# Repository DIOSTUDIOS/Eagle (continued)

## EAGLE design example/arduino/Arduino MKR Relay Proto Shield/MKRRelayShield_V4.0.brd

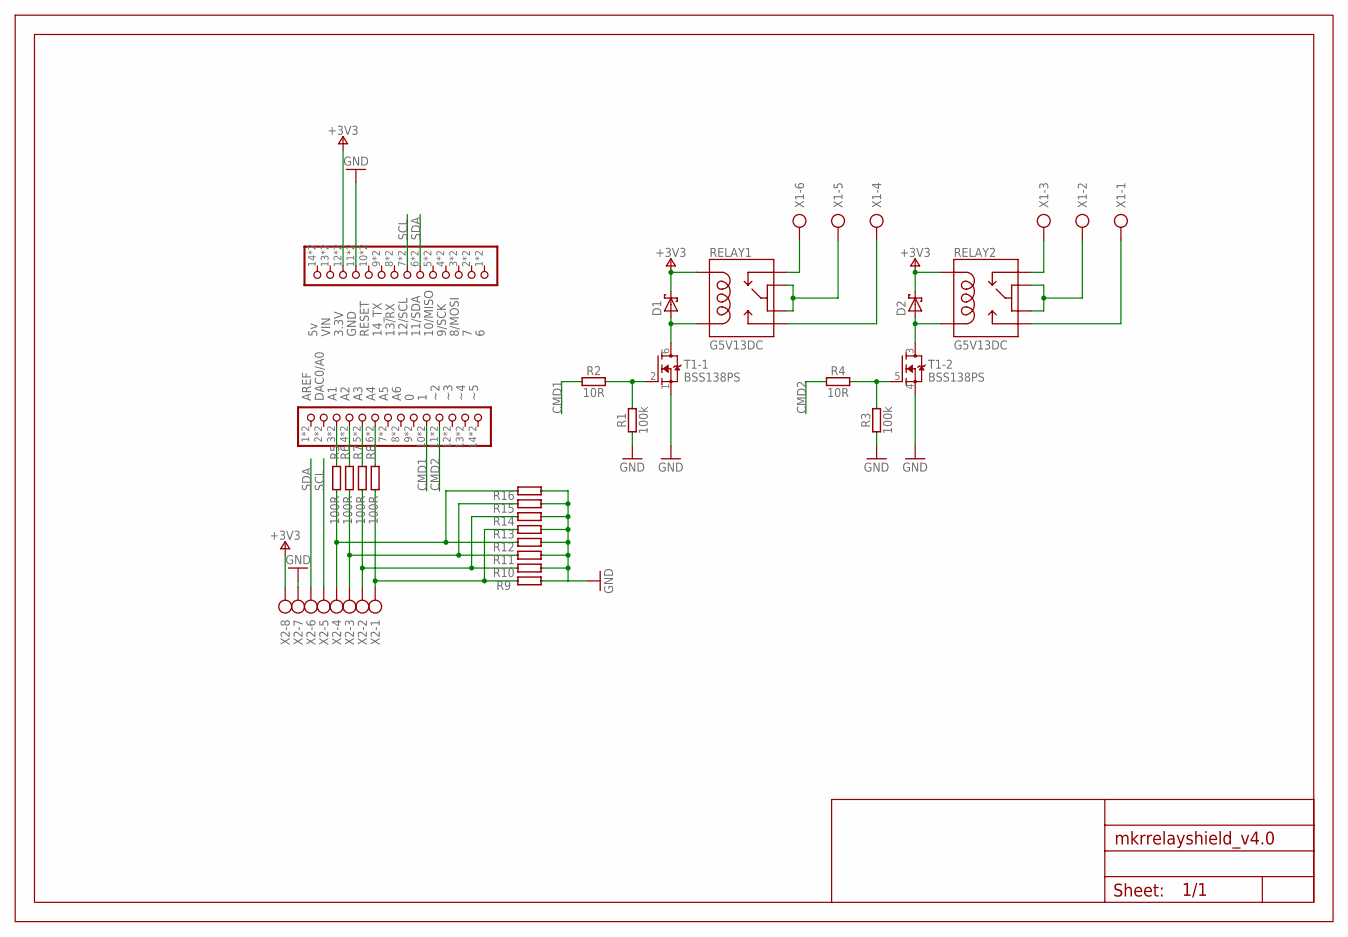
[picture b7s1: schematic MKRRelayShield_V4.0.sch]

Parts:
D1, D2: D_SCHOTTKYSO123; SMA_DO123
FRAME1: DNP; FRAME
JP3, JP4: PINHD-1X14DOUBLE; 1X14-DOUBLE
R1, R3: 100k; 0402-1005X55N
R2, R4: 10R; 0402-1005X55N
R5, R6, R7, R8, R13, R14, R15, R16: 100R; 0805-R2013X50N
R9, R10, R11, R12: 10k; 0204V
RELAY1, RELAY2: G5V13DC; RELAY-G5V
T1: BSS138PS; SOT363
X1: AK300/6
X2: AK300/8

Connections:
+3V3: D1.C, D2.C, JP4.12, JP4.26 (12), RELAY1.2, RELAY2.2, X2.8
CMD1: JP3.10, JP3.24 (10), R2.1
CMD2: JP3.11, JP3.25 (11), R4.1
GND: JP4.11, JP4.25 (11), R1.1, R3.1, R9.1, R10.1, R11.1, R12.1, R13.1, R14.1, R15.1, R16.1, T1.1 (S), T1.4 (S), X2.7
unnamed: JP3.6, JP3.20 (6), R8.2
unnamed: R5.1, R12.2, R16.2, X2.4
unnamed: JP3.5, JP3.19 (5), R7.2
unnamed: JP3.4, JP3.18 (4), R6.2
unnamed: JP3.3, JP3.17 (3), R5.2
unnamed: R6.1, R11.2, R15.2, X2.3
unnamed: R7.1, R10.2, R14.2, X2.2
unnamed: R8.1, R9.2, R13.2, X2.1
unnamed: RELAY1.5, RELAY1.6, X1.5
unnamed: D1.A, RELAY1.9, T1.6 (D)
unnamed: RELAY2.5, RELAY2.6, X1.2
unnamed: D2.A, RELAY2.9, T1.3 (D)
unnamed: RELAY1.1, X1.6
unnamed: RELAY1.10, X1.4
unnamed: RELAY2.1, X1.3
unnamed: RELAY2.10, X1.1
unnamed: R1.2, R2.2, T1.2 (G)
unnamed: R3.2, R4.2, T1.5 (G)
SCL: JP4.7, JP4.21 (7), X2.5
SDA: JP4.6, JP4.20 (6), X2.6

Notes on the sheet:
AREF
DAC0/A0
8/MOSI
9/SCK
10/MISO
11/SDA
12/SCL
13/RX
14_TX
RESET
GND
3.3V
VIN

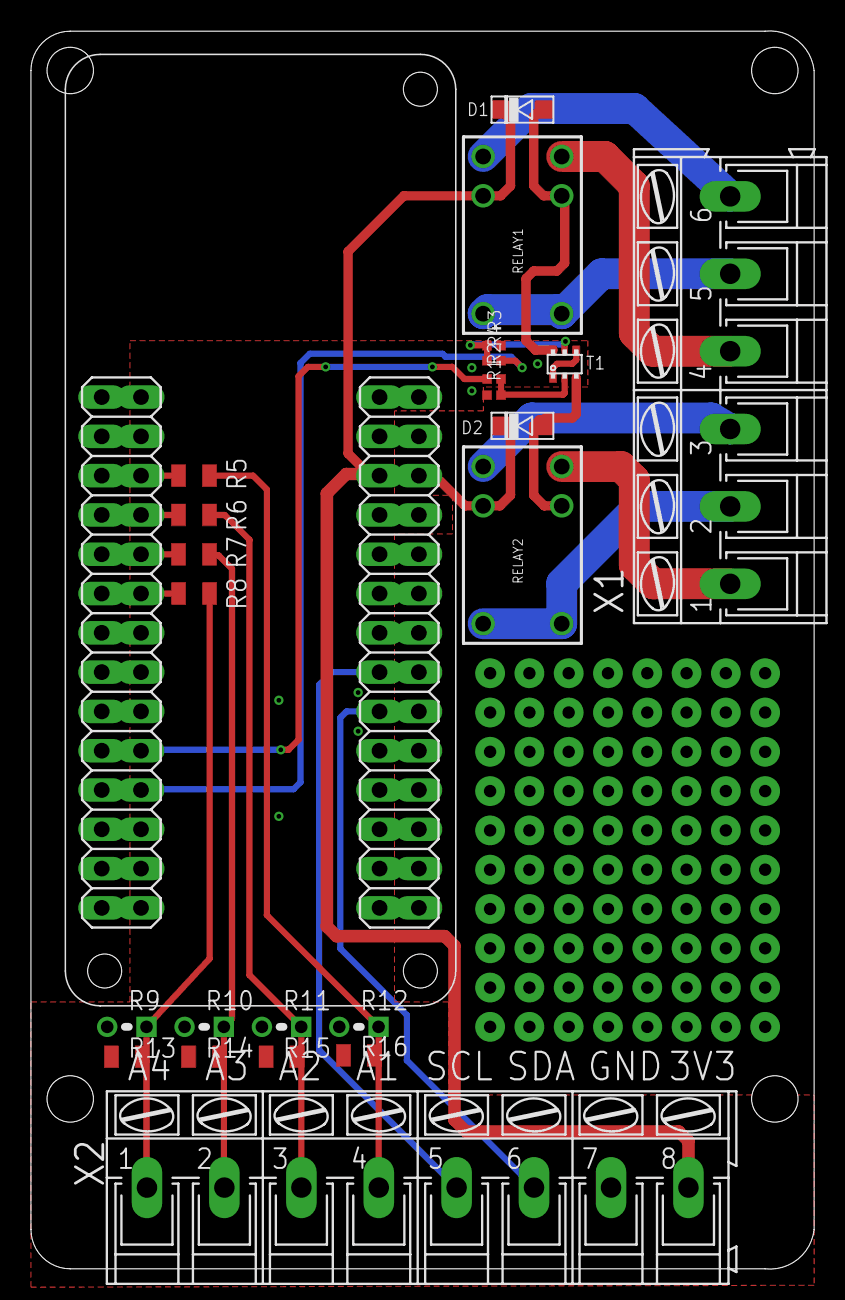
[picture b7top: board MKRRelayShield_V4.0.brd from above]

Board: 2 copper layers, 50.6 x 80.0 mm, 26 parts (0 on the bottom side), 24 nets.

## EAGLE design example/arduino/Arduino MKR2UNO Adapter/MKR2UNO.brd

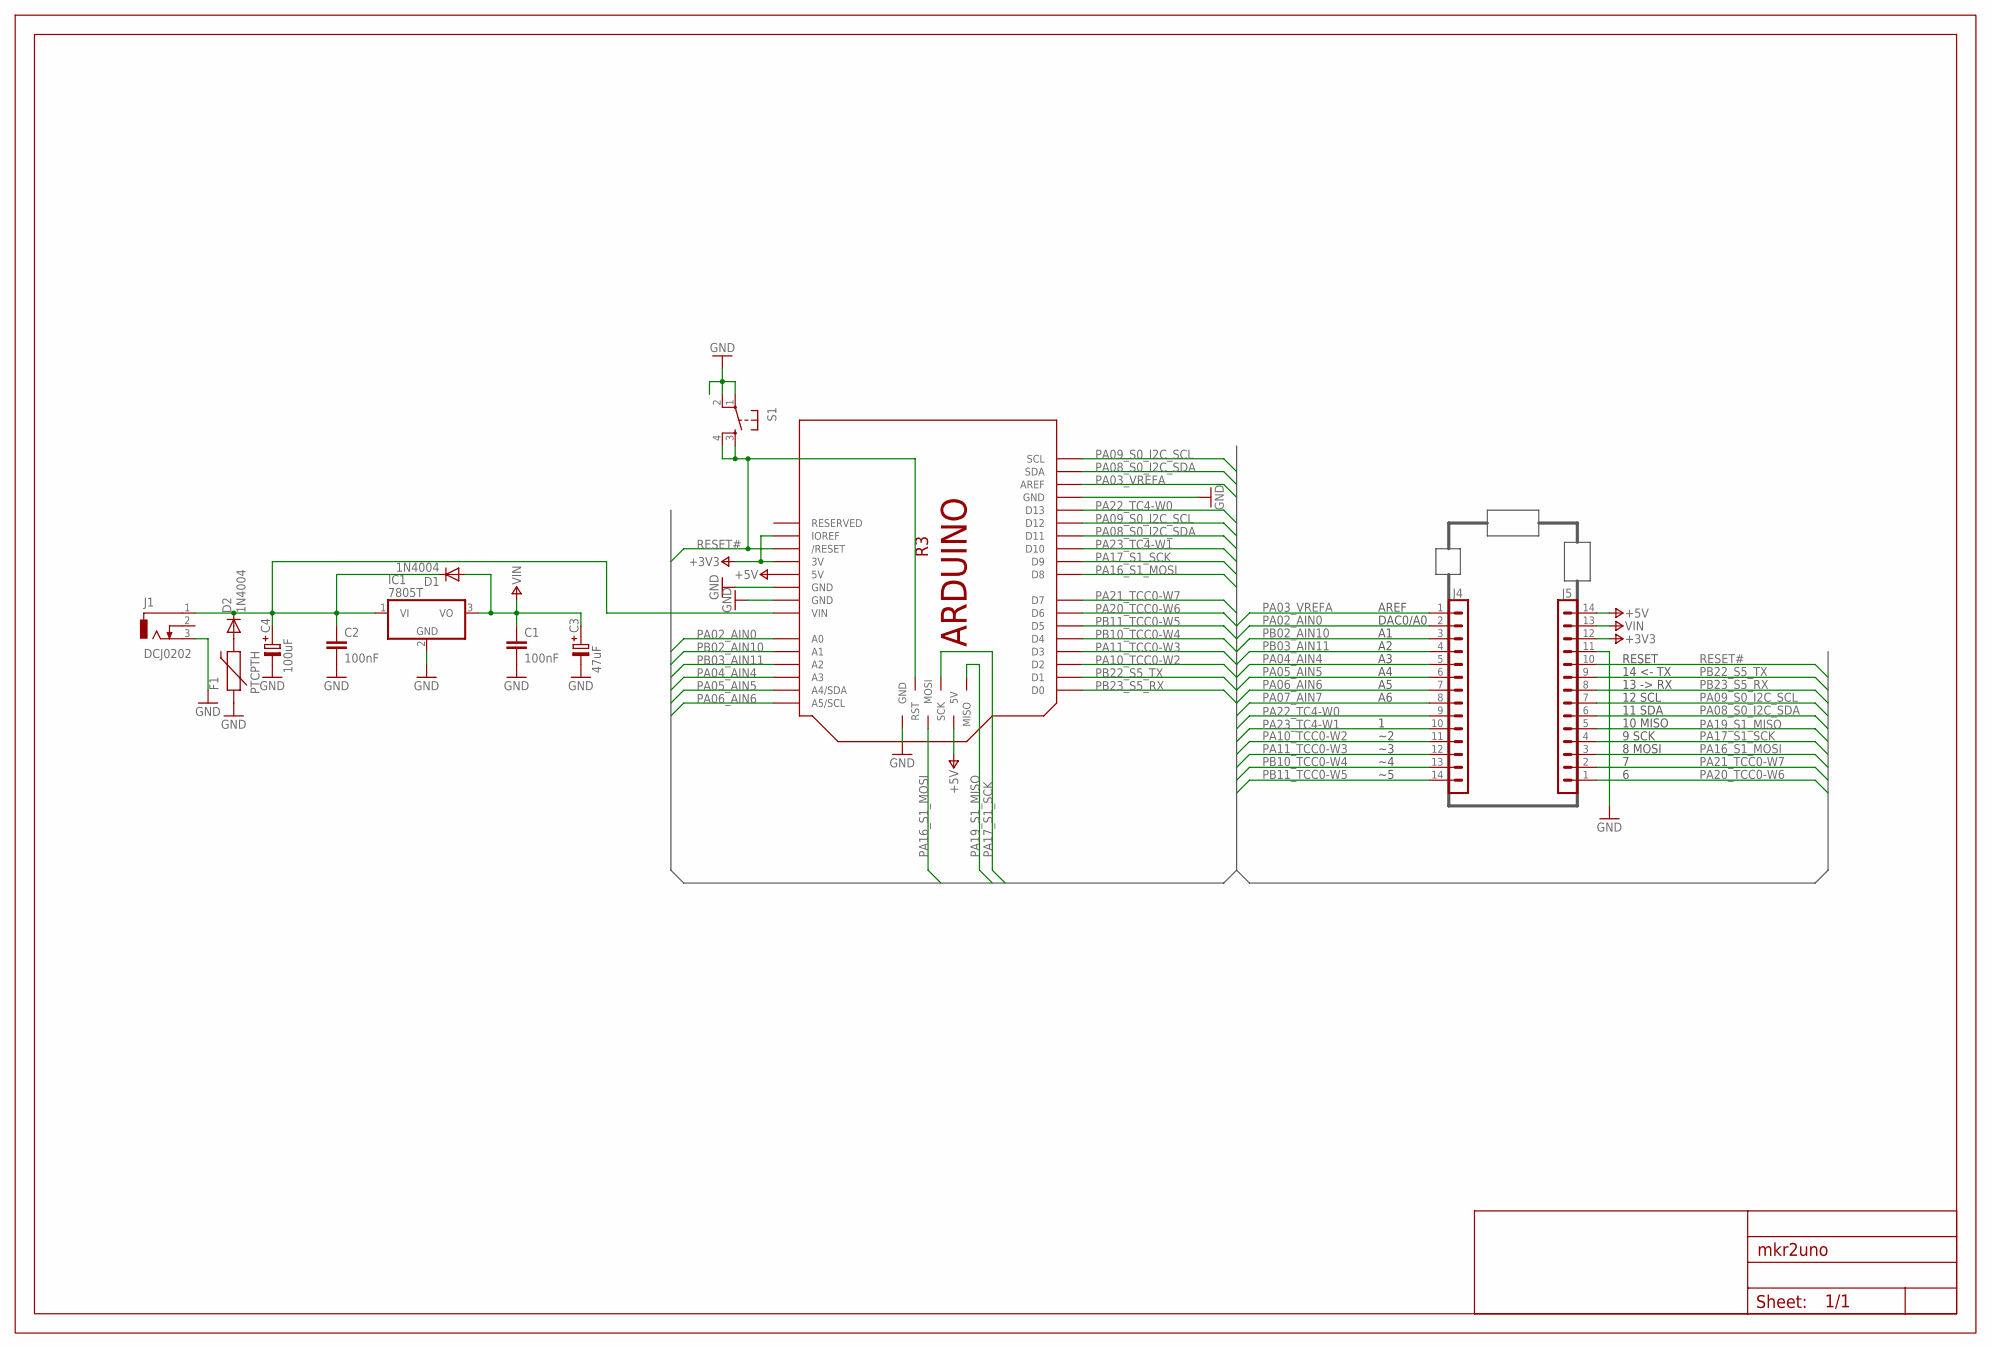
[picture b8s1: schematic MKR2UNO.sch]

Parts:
C1, C2: 100nF; C025-024X044
C3: 47uF; EA6,3-10
C4: 100uF; EA6,3-10
D1, D2: 1N4004; DO41-10
F1: PTCPTH; PTC
FRAME1: Page 1; FRAME
IC1: 7805T; TO220H
J1: DCJ0202
J4, J5: DNP; 1X14
M1: ARDUINO_R3_ICSP; ARDUINOR3_ICSP
S1: TAC_SWITCHPTH; TACTILE-PTH

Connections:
+3V3: J5.12, M1.3V, M1.IOREF
+5V: J5.14, M1.5V, M1.5V_ICSP (5V)
GND: C1.2, C2.2, C3.-, C4.-, F1.P$1 (1), IC1.2 (GND), J1.3, J5.11, M1.GND, M1.GND@1 (GND), M1.GND@2 (GND), M1.GND@3 (GND), S1.1, S1.2
unnamed: C2.1, C4.+, D1.C, D2.C, IC1.1 (VI), J1.1, M1.VIN
unnamed: D2.A, F1.P$2 (2)
PA02_AIN0: J4.2, M1.A0
PA03_VREFA: J4.1, M1.AREF
PA04_AIN4: J4.5, M1.A3
PA05_AIN5: J4.6, M1.A4 (A4/SDA)
PA06_AIN6: J4.7, M1.A5 (A5/SCL)
PA07_AIN7: J4.8
PA08_S0_I2C_SDA: J5.6, M1.D11, M1.SDA
PA09_S0_I2C_SCL: J5.7, M1.D12, M1.SCL
PA10_TCC0-W2: J4.11, M1.D2
PA11_TCC0-W3: J4.12, M1.D3
PA16_S1_MOSI: J5.3, M1.D8, M1.MOSI
PA17_S1_SCK: J5.4, M1.D9, M1.SCK
PA19_S1_MISO: J5.5, M1.MISO
PA20_TCC0-W6: J5.1, M1.D6
PA21_TCC0-W7: J5.2, M1.D7
PA22_TC4-W0: J4.9, M1.D13
PA23_TC4-W1: J4.10, M1.D10
PB02_AIN10: J4.3, M1.A1
PB03_AIN11: J4.4, M1.A2
PB10_TCC0-W4: J4.13, M1.D4
PB11_TCC0-W5: J4.14, M1.D5
PB22_S5_TX: J5.9, M1.D1
PB23_S5_RX: J5.8, M1.D0
RESET#: J5.10, M1.RESET (/RESET), M1.RESET_ICSP (RST), S1.3, S1.4
VIN: C1.1, C3.+, D1.A, IC1.3 (VO), J5.13

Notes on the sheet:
14 <- TX
13 -> RX
12 SCL
RESET
11 SDA
8 MOSI
9 SCK
10 MISO
AREF
DAC0/A0

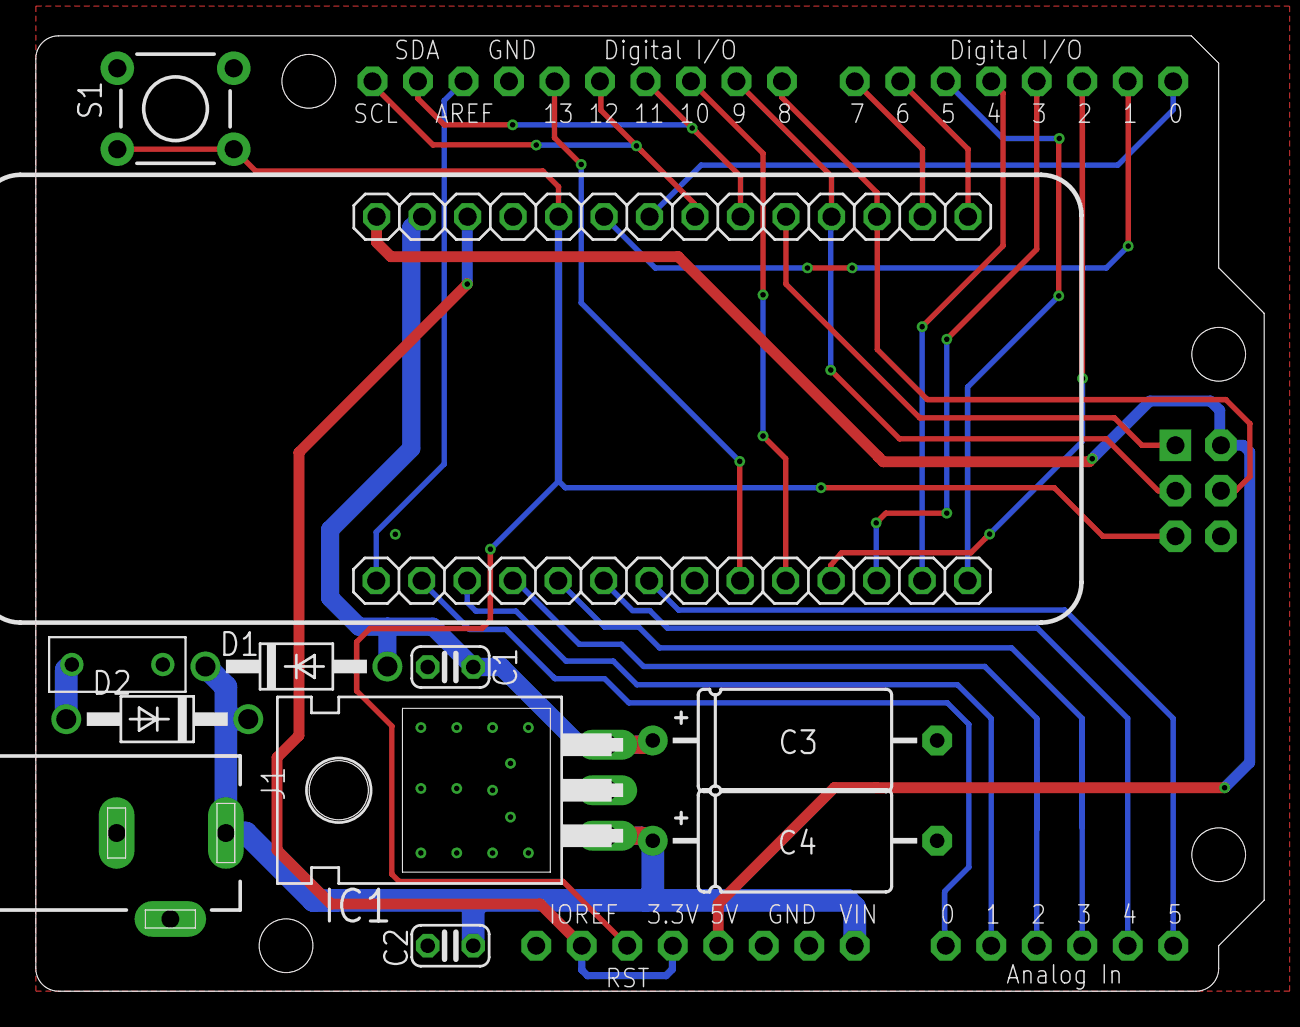
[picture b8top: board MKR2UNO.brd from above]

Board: 2 copper layers, 68.6 x 53.3 mm, 14 parts (0 on the bottom side), 29 nets.
